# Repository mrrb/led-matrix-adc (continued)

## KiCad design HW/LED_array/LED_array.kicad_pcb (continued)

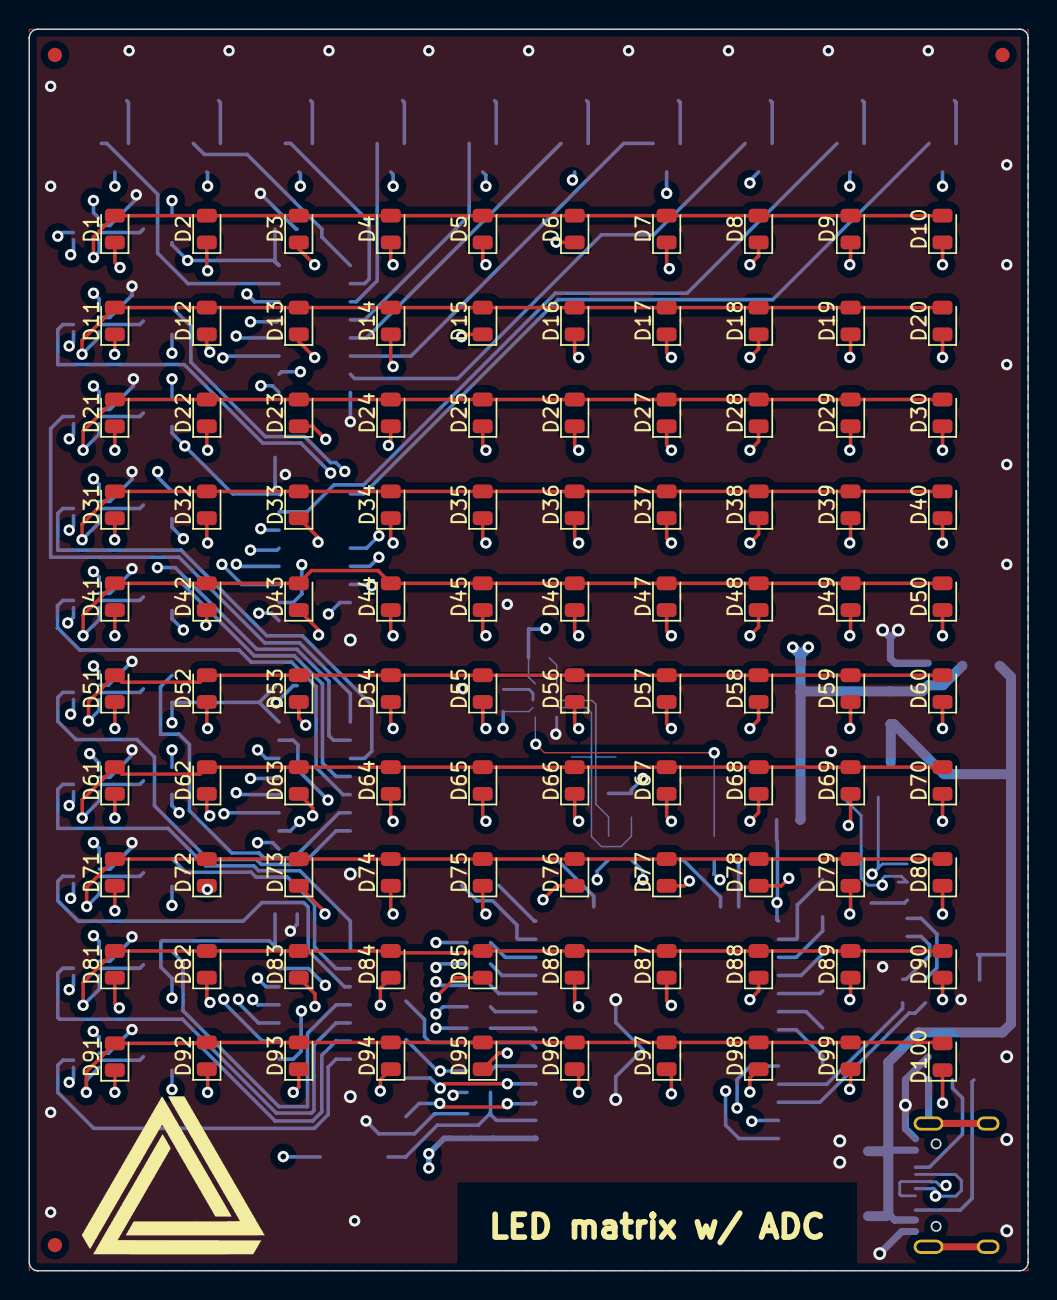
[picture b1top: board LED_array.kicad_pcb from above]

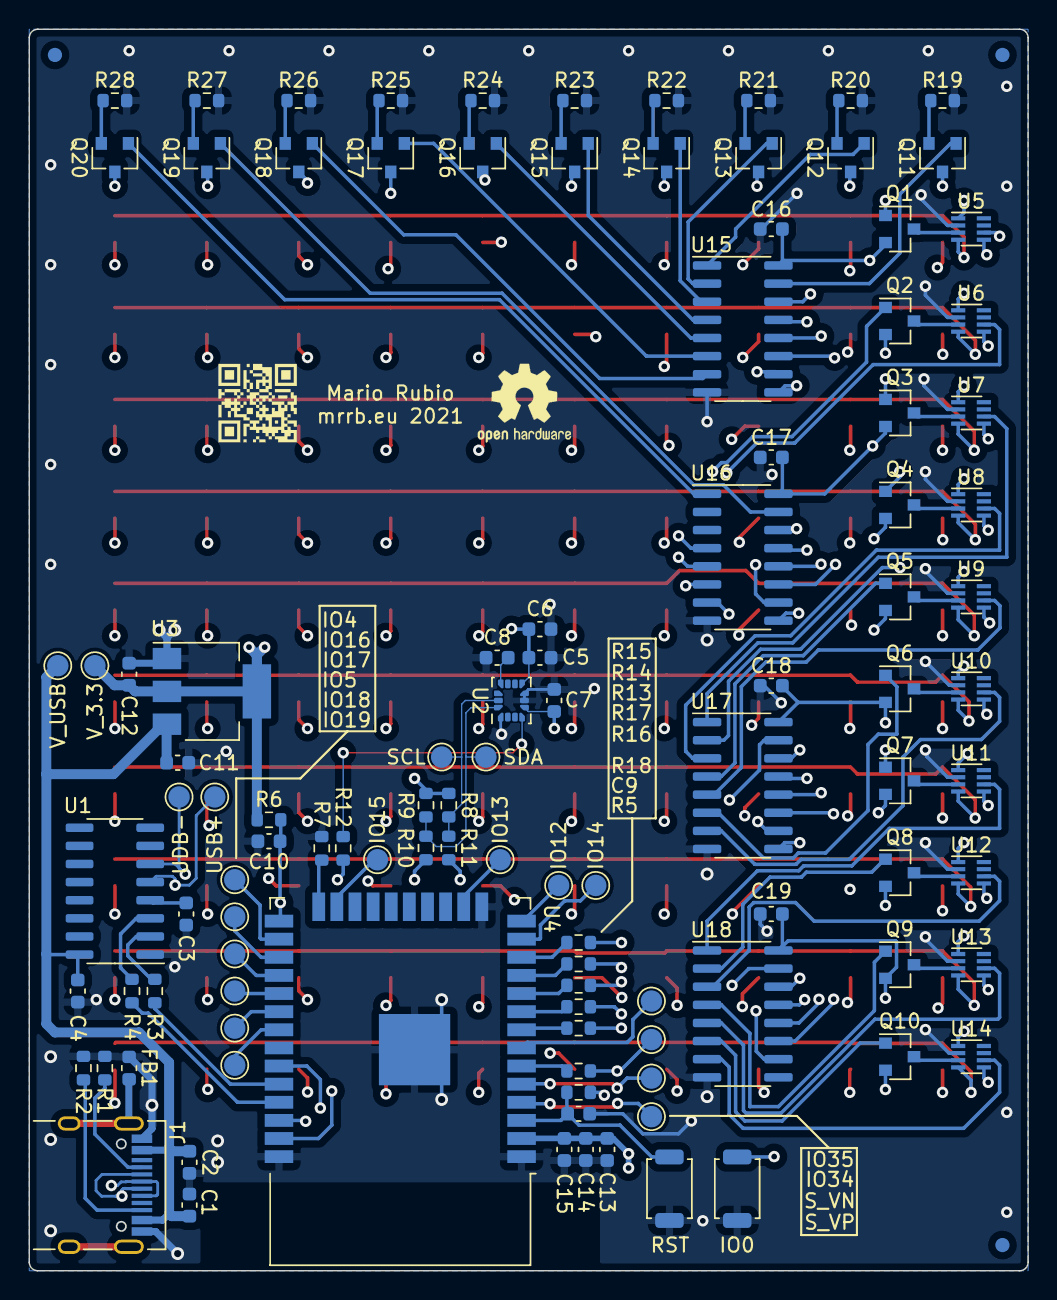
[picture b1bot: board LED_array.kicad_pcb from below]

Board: 4 copper layers, 70.0 x 87.0 mm, 218 parts (114 on the bottom side), 121 nets.

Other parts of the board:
FD1, FD2, FD3, FD4, FD5, FD6: Fiducial_1mm_Mask2mm
OH_logo: OSHW-Logo2_7.3x6mm_SilkScreen
QR: LOGO; qr2
penrose_logo: LOGO; penrose1

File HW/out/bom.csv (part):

"Source:","/home/mra/Sync/PC_sync/Projects/LED_array/LED_array/LED_array.kicad_sch"
"Date:","dom 06 jun 2021 13:36:47"
"Tool:","Eeschema (5.99.0-10847-g28909c1a72)"
"Generator:","/usr/share/kicad-nightly/plugins/bom_csv_grouped_by_value.py"
"Component Count:","189"

"Individual Components:"

"Item","Qty","Reference(s)","Value","LibPart","Footprint","Datasheet","LCSC","LCSC part"
"","","C1","1u","Device:C_Small","Capacitor_SMD:C_0603_1608Metric","~","",""
"","","C2","100n","Device:C_Small","Capacitor_SMD:C_0603_1608Metric","~","",""
"","","C3","100n","Device:C_Small","Capacitor_SMD:C_0603_1608Metric","~","",""
"","","C4","100n","Device:C_Small","Capacitor_SMD:C_0603_1608Metric","~","",""
"","","C5","1u","Device:C_Small","Capacitor_SMD:C_0603_1608Metric","~","",""
"","","C6","100n","Device:C_Small","Capacitor_SMD:C_0603_1608Metric","~","",""
"","","C7","100n","Device:C_Small","Capacitor_SMD:C_0603_1608Metric","~","",""
"","","C8","100n","Device:C_Small","Capacitor_SMD:C_0603_1608Metric","~","",""
"","","C9","100n","Device:C_Small","Capacitor_SMD:C_0603_1608Metric","~","",""
"","","C10","100n","Device:C_Small","Capacitor_SMD:C_0603_1608Metric","~","",""
"","","C11","1u","Device:C_Small","Capacitor_SMD:C_0603_1608Metric","~","",""
"","","C12","1u","Device:C_Small","Capacitor_SMD:C_0603_1608Metric","~","",""
"","","C13","1u","Device:C_Small","Capacitor_SMD:C_0603_1608Metric","~","",""
"","","C14","100n","Device:C_Small","Capacitor_SMD:C_0603_1608Metric","~","",""
"","","C15","100n","Device:C_Small","Capacitor_SMD:C_0603_1608Metric","~","",""
"","","C16","100n","Device:C_Small","Capacitor_SMD:C_0603_1608Metric","~","",""
"","","C17","100n","Device:C_Small","Capacitor_SMD:C_0603_1608Metric","~","",""
"","","C18","100n","Device:C_Small","Capacitor_SMD:C_0603_1608Metric","~","",""
"","","C19","100n","Device:C_Small","Capacitor_SMD:C_0603_1608Metric","~","",""
"","","D1","LED_Small_ALT","Device:LED_Small_ALT","LED_SMD:LED_0805_2012Metric","~","",""
"","","D2","LED_Small_ALT","Device:LED_Small_ALT","LED_SMD:LED_0805_2012Metric","~","",""
"","","D3","LED_Small_ALT","Device:LED_Small_ALT","LED_SMD:LED_0805_2012Metric","~","",""
"","","D4","LED_Small_ALT","Device:LED_Small_ALT","LED_SMD:LED_0805_2012Metric","~","",""
"","","D5","LED_Small_ALT","Device:LED_Small_ALT","LED_SMD:LED_0805_2012Metric","~","",""
"","","D6","LED_Small_ALT","Device:LED_Small_ALT","LED_SMD:LED_0805_2012Metric","~","",""
"","","D7","LED_Small_ALT","Device:LED_Small_ALT","LED_SMD:LED_0805_2012Metric","~","",""
"","","D8","LED_Small_ALT","Device:LED_Small_ALT","LED_SMD:LED_0805_2012Metric","~","",""
"","","D9","LED_Small_ALT","Device:LED_Small_ALT","LED_SMD:LED_0805_2012Metric","~","",""
"","","D10","LED_Small_ALT","Device:LED_Small_ALT","LED_SMD:LED_0805_2012Metric","~","",""
"","","D11","LED_Small_ALT","Device:LED_Small_ALT","LED_SMD:LED_0805_2012Metric","~","",""
"","","D12","LED_Small_ALT","Device:LED_Small_ALT","LED_SMD:LED_0805_2012Metric","~","",""
"","","D13","LED_Small_ALT","Device:LED_Small_ALT","LED_SMD:LED_0805_2012Metric","~","",""
"","","D14","LED_Small_ALT","Device:LED_Small_ALT","LED_SMD:LED_0805_2012Metric","~","",""
"","","D15","LED_Small_ALT","Device:LED_Small_ALT","LED_SMD:LED_0805_2012Metric","~","",""
"","","D16","LED_Small_ALT","Device:LED_Small_ALT","LED_SMD:LED_0805_2012Metric","~","",""
"","","D17","LED_Small_ALT","Device:LED_Small_ALT","LED_SMD:LED_0805_2012Metric","~","",""
"","","D18","LED_Small_ALT","Device:LED_Small_ALT","LED_SMD:LED_0805_2012Metric","~","",""
"","","D19","LED_Small_ALT","Device:LED_Small_ALT","LED_SMD:LED_0805_2012Metric","~","",""
"","","D20","LED_Small_ALT","Device:LED_Small_ALT","LED_SMD:LED_0805_2012Metric","~","",""
"","","D21","LED_Small_ALT","Device:LED_Small_ALT","LED_SMD:LED_0805_2012Metric","~","",""
"","","D22","LED_Small_ALT","Device:LED_Small_ALT","LED_SMD:LED_0805_2012Metric","~","",""
"","","D23","LED_Small_ALT","Device:LED_Small_ALT","LED_SMD:LED_0805_2012Metric","~","",""
"","","D24","LED_Small_ALT","Device:LED_Small_ALT","LED_SMD:LED_0805_2012Metric","~","",""
"","","D25","LED_Small_ALT","Device:LED_Small_ALT","LED_SMD:LED_0805_2012Metric","~","",""
"","","D26","LED_Small_ALT","Device:LED_Small_ALT","LED_SMD:LED_0805_2012Metric","~","",""
"","","D27","LED_Small_ALT","Device:LED_Small_ALT","LED_SMD:LED_0805_2012Metric","~","",""
"","","D28","LED_Small_ALT","Device:LED_Small_ALT","LED_SMD:LED_0805_2012Metric","~","",""
"","","D29","LED_Small_ALT","Device:LED_Small_ALT","LED_SMD:LED_0805_2012Metric","~","",""
"","","D30","LED_Small_ALT","Device:LED_Small_ALT","LED_SMD:LED_0805_2012Metric","~","",""
"","","D31","LED_Small_ALT","Device:LED_Small_ALT","LED_SMD:LED_0805_2012Metric","~","",""
"","","D32","LED_Small_ALT","Device:LED_Small_ALT","LED_SMD:LED_0805_2012Metric","~","",""
"","","D33","LED_Small_ALT","Device:LED_Small_ALT","LED_SMD:LED_0805_2012Metric","~","",""
"","","D34","LED_Small_ALT","Device:LED_Small_ALT","LED_SMD:LED_0805_2012Metric","~","",""
"","","D35","LED_Small_ALT","Device:LED_Small_ALT","LED_SMD:LED_0805_2012Metric","~","",""
"","","D36","LED_Small_ALT","Device:LED_Small_ALT","LED_SMD:LED_0805_2012Metric","~","",""
"","","D37","LED_Small_ALT","Device:LED_Small_ALT","LED_SMD:LED_0805_2012Metric","~","",""
"","","D38","LED_Small_ALT","Device:LED_Small_ALT","LED_SMD:LED_0805_2012Metric","~","",""
"","","D39","LED_Small_ALT","Device:LED_Small_ALT","LED_SMD:LED_0805_2012Metric","~","",""
"","","D40","LED_Small_ALT","Device:LED_Small_ALT","LED_SMD:LED_0805_2012Metric","~","",""
"","","D41","LED_Small_ALT","Device:LED_Small_ALT","LED_SMD:LED_0805_2012Metric","~","",""
"","","D42","LED_Small_ALT","Device:LED_Small_ALT","LED_SMD:LED_0805_2012Metric","~","",""
"","","D43","LED_Small_ALT","Device:LED_Small_ALT","LED_SMD:LED_0805_2012Metric","~","",""
"","","D44","LED_Small_ALT","Device:LED_Small_ALT","LED_SMD:LED_0805_2012Metric","~","",""
"","","D45","LED_Small_ALT","Device:LED_Small_ALT","LED_SMD:LED_0805_2012Metric","~","",""
"","","D46","LED_Small_ALT","Device:LED_Small_ALT","LED_SMD:LED_0805_2012Metric","~","",""
"","","D47","LED_Small_ALT","Device:LED_Small_ALT","LED_SMD:LED_0805_2012Metric","~","",""
"","","D48","LED_Small_ALT","Device:LED_Small_ALT","LED_SMD:LED_0805_2012Metric","~","",""
"","","D49","LED_Small_ALT","Device:LED_Small_ALT","LED_SMD:LED_0805_2012Metric","~","",""
"","","D50","LED_Small_ALT","Device:LED_Small_ALT","LED_SMD:LED_0805_2012Metric","~","",""
"","","D51","LED_Small_ALT","Device:LED_Small_ALT","LED_SMD:LED_0805_2012Metric","~","",""
"","","D52","LED_Small_ALT","Device:LED_Small_ALT","LED_SMD:LED_0805_2012Metric","~","",""
"","","D53","LED_Small_ALT","Device:LED_Small_ALT","LED_SMD:LED_0805_2012Metric","~","",""
"","","D54","LED_Small_ALT","Device:LED_Small_ALT","LED_SMD:LED_0805_2012Metric","~","",""
"","","D55","LED_Small_ALT","Device:LED_Small_ALT","LED_SMD:LED_0805_2012Metric","~","",""
"","","D56","LED_Small_ALT","Device:LED_Small_ALT","LED_SMD:LED_0805_2012Metric","~","",""
"","","D57","LED_Small_ALT","Device:LED_Small_ALT","LED_SMD:LED_0805_2012Metric","~","",""
"","","D58","LED_Small_ALT","Device:LED_Small_ALT","LED_SMD:LED_0805_2012Metric","~","",""
"","","D59","LED_Small_ALT","Device:LED_Small_ALT","LED_SMD:LED_0805_2012Metric","~","",""
"","","D60","LED_Small_ALT","Device:LED_Small_ALT","LED_SMD:LED_0805_2012Metric","~","",""
"","","D61","LED_Small_ALT","Device:LED_Small_ALT","LED_SMD:LED_0805_2012Metric","~","",""
"","","D62","LED_Small_ALT","Device:LED_Small_ALT","LED_SMD:LED_0805_2012Metric","~","",""
"","","D63","LED_Small_ALT","Device:LED_Small_ALT","LED_SMD:LED_0805_2012Metric","~","",""
"","","D64","LED_Small_ALT","Device:LED_Small_ALT","LED_SMD:LED_0805_2012Metric","~","",""
"","","D65","LED_Small_ALT","Device:LED_Small_ALT","LED_SMD:LED_0805_2012Metric","~","",""
"","","D66","LED_Small_ALT","Device:LED_Small_ALT","LED_SMD:LED_0805_2012Metric","~","",""
"","","D67","LED_Small_ALT","Device:LED_Small_ALT","LED_SMD:LED_0805_2012Metric","~","",""
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
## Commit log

2021-06-06 Add schematic+pcb REV1
2021-06-06 Init SW
2021-06-06 Quick change
2021-06-06 Add gerber, bom and schematic/pcb PDFs
